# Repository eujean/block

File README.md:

Possibly over-engineered binary clock with temperature display.

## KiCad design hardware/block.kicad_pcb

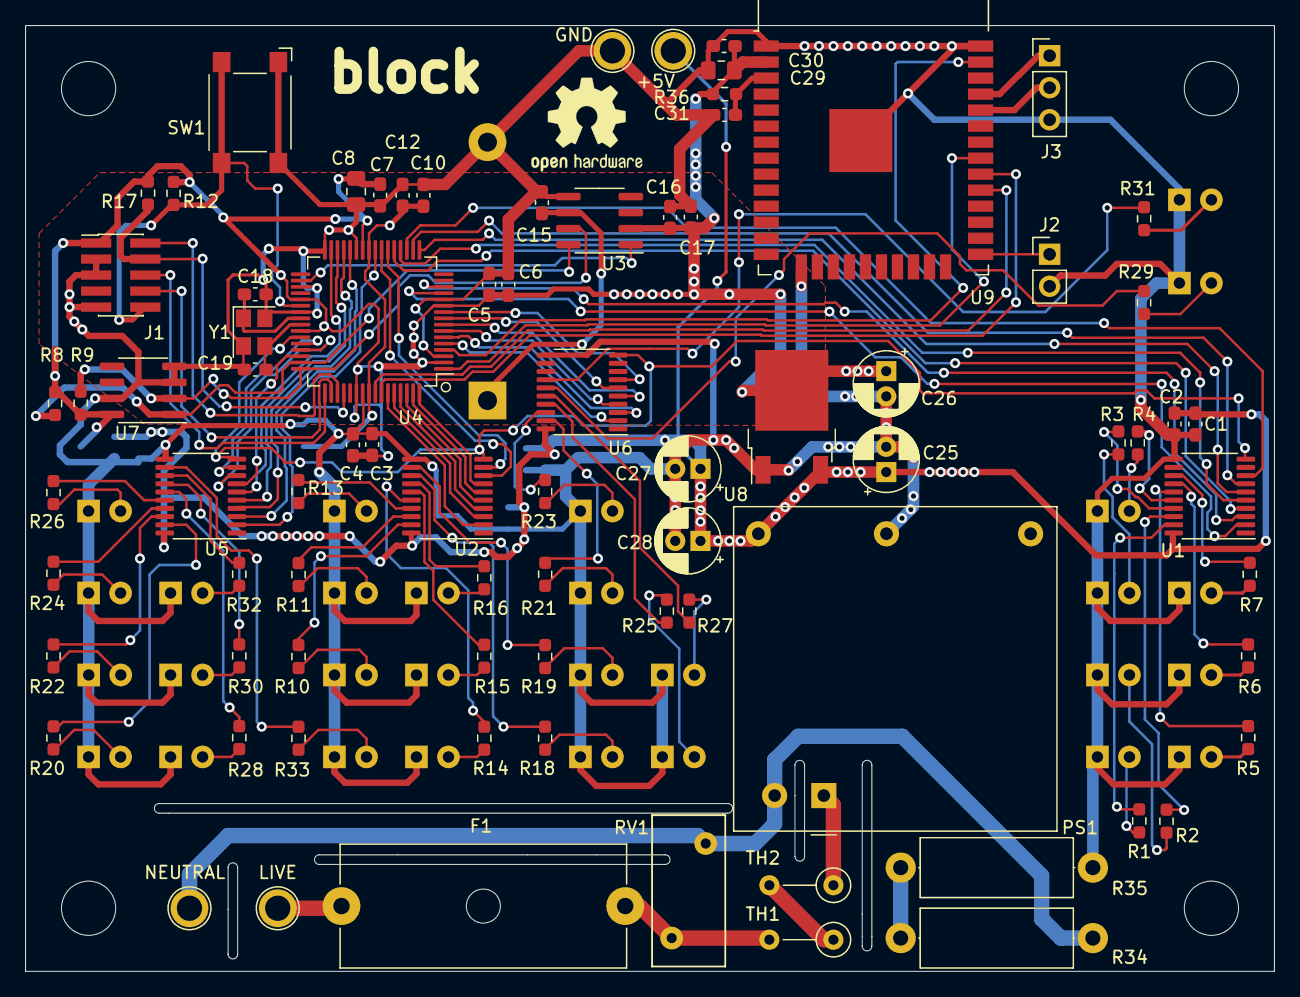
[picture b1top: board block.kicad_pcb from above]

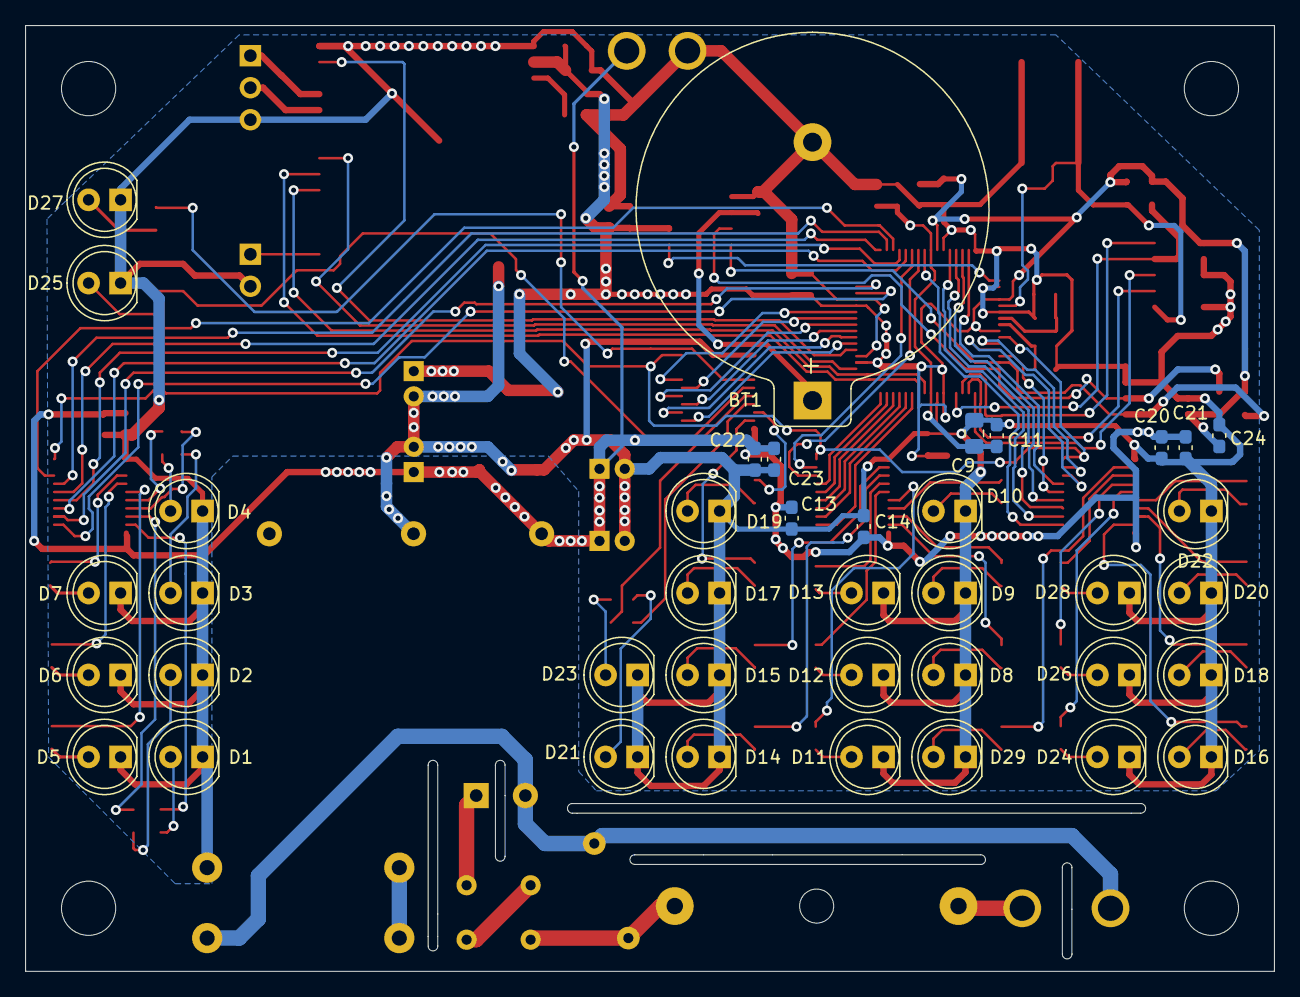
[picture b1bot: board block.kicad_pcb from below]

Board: 2 copper layers, 99.0 x 75.0 mm, 124 parts (39 on the bottom side), 117 nets.

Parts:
+5V: +5; TestPoint_Plated_Hole_D2.0mm
BT1: Battery_Cell; BatteryHolder_Keystone_106_1x20mm
C1, C10, C13, C17, C20, C22, C31: 1uF; C_0603_1608Metric_Pad1.08x0.95mm_HandSolder
C2, C3, C5, C7, C11, C12, C14, C15, C16, C21, C23, C24, C30: 0.1uF; C_0603_1608Metric_Pad1.08x0.95mm_HandSolder
C4, C6: 0.01uF; C_0603_1608Metric_Pad1.08x0.95mm_HandSolder
C8: 1uF; C_0805_2012Metric_Pad1.18x1.45mm_HandSolder
C9: 2.2uF; C_0805_2012Metric_Pad1.18x1.45mm_HandSolder
C18, C19: 10pF; C_0603_1608Metric_Pad1.08x0.95mm_HandSolder
C25, C28: 10uF; CP_Radial_D5.0mm_P2.00mm
C26: 100uF; CP_Radial_D5.0mm_P2.00mm
C27: 1.0uF; CP_Radial_D5.0mm_P2.00mm
C29: 10uF; C_0805_2012Metric_Pad1.18x1.45mm_HandSolder
D1, D2, D3, D4, D5, D6, D7, D8, D9, D10, D11, D12, D13, D14, D15, D16, D17, D18, D19, D20, D21, D22, D23, D24, D25, D26, D27, D28, D29: LED; LED_D5.0mm
F1: Fuse; Fuseholder_Cylinder-5x20mm_Schurter_0031_8201_Horizontal_Op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
GND: GND; TestPoint_Plated_Hole_D2.0mm
H1, H2, H3, H4: MountingHole; MountingHole_4.3mm_M4
J1: Conn_ARM_JTAG_SWD_10; PinHeader_2x05_P1.27mm_Vertical_SMD
J2: Conn_01x02_Female; PinHeader_1x02_P2.54mm_Vertical
J3: Conn_01x03; PinHeader_1x03_P2.54mm_Vertical
LIVE: LIVE; TestPoint_Plated_Hole_D2.0mm
NEUTRAL: NEUTRAL; TestPoint_Plated_Hole_D2.0mm
PS1: RAC05-05SK; Converter_ACDC_RECOM_RAC05-xxSK_THT
R1, R2, R3, R4, R5, R6, R7, R10, R11, R13, R14, R15, R16, R18, R19, R20, R21, R22, R23, R24, R25, R26, R27, R28, R29, R30, R31, R32, R33: R; R_0603_1608Metric_Pad0.98x0.95mm_HandSolder
R8, R9: 2.2k; R_0603_1608Metric_Pad0.98x0.95mm_HandSolder
R12, R17, R36: 10k; R_0603_1608Metric_Pad0.98x0.95mm_HandSolder
R34, R35: 560k; R_Axial_DIN0414_L11.9mm_D4.5mm_P15.24mm_Horizontal
RV1: Varistor; RV_Disc_D12mm_W5.8mm_P7.5mm
SW1: SW_Push4; SW_SPST_Omron_B3FS-100xP
TH1, TH2: 20R; R_Axial_DIN0207_L6.3mm_D2.5mm_P5.08mm_Vertical
U1, U2, U5, U6: TLC59213; TSSOP-20_4.4x6.5mm_P0.65mm
U3: DS3232M; SOIC-8_3.9x4.9mm_P1.27mm
U4: TM4C1231E6PM; LQFP-64_10x10mm_P0.5mm
U7: ADT7410; SOIC-8_3.9x4.9mm_P1.27mm
U8: LM1117-3.3; TO-252-2
U9: ESP32-WROOM-32
Y1: Crystal_GND24_Small; Crystal_SMD_Abracon_ABM8G-4Pin_3.2x2.5mm

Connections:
32kHz: U3.1, U4.34
+3V3: C3.1, C4.1, C5.1, C6.1, C7.1, C8.1, C16.1, C17.1, C24.1, C26.1, C29.1, C30.1, J1.1, R8.1, R9.1, R12.1, R17.1, R36.1, U3.2, U4.2, U4.11, U4.26, U4.37, U4.42, U4.54, U7.8, U8.2, U9.2
+5V: +5V.1, C1.1, C2.1, C13.1, C14.1, C20.1, C21.1, C22.1, C23.1, C25.1, C27.1, C28.1, PS1.5, U1.20, U2.20, U5.20, U6.20, U8.3
/Vddc: C9.1, C10.1, C11.1, C12.1, U4.25, U4.56
CS: U4.57, U9.29
GND: BT1.2, C1.2, C2.2, C3.2, C4.2, C5.2, C6.2, C7.2, C8.2, C9.2, C10.2, C11.2, C12.2, C13.2, C14.2, C15.2, C16.2, C17.2, C18.2, C19.2, C20.2, C21.2, C22.2, C23.2, C24.2, C25.2, C26.2, C27.2, C28.2, C29.2, C30.2, C31.2, D1.1, D2.1, D3.1, D4.1, D5.1, D6.1, D7.1, D8.1, D9.1, D10.1, D11.1, D12.1, D13.1, D14.1, D15.1, D16.1, D17.1, D18.1, D19.1, D20.1, D21.1, D22.1, D23.1, D24.1, D25.1, D26.1, D27.1, D28.1, D29.1, GND.1, J1.3, J1.5, J1.9, J2.2, J3.3, PS1.4, R35.1, SW1.1, SW1.2, U1.11, U2.11, U3.5, U4.3, U4.12, U4.27, U4.32, U4.35, U4.39, U4.55, U5.11, U6.11, U7.3, U7.4, U7.7, U8.1, U9.1, U9.15, U9.38, U9.39, Y1.2, Y1.4
HR01: U2.8, U4.23
HR02: U2.9, U4.22
HR04: U4.5, U6.2
HR08: U4.6, U6.3
HR11: U4.7, U6.4
HR12: U4.8, U6.5
I2C_SCL: R8.2, U3.8, U4.47, U7.1
I2C_SDA: R9.2, U3.7, U4.48, U7.2
LED_CLK: U1.10, U2.10, U4.43, U5.10, U6.10
MIN01: U4.44, U5.9
MIN02: U2.2, U4.59
MIN04: U2.3, U4.60
MIN08: U2.4, U4.61
MIN11: U2.5, U4.62
MIN12: U2.6, U4.63
MIN14: U2.7, U4.64
MISO: U4.1, U9.31
MOSI: U4.4, U9.37
unnamed: BT1.1, C15.1, U3.6
unnamed: C18.1, U4.40, Y1.1
unnamed: C19.1, U4.41, Y1.3
unnamed: C31.1, R36.2, U9.3
unnamed: D1.2, R1.1
unnamed: D2.2, R2.1
unnamed: D3.2, R3.1
unnamed: D4.2, R4.1
unnamed: D5.2, R5.1
unnamed: D6.2, R6.1
unnamed: D7.2, R7.1
unnamed: D8.2, R10.1
unnamed: D9.2, R11.1
unnamed: D10.2, R13.1
unnamed: D11.2, R14.1
unnamed: D12.2, R15.1
unnamed: D13.2, R16.1
unnamed: D14.2, R18.1
unnamed: D15.2, R19.1
unnamed: D16.2, R20.1
unnamed: D17.2, R21.1
unnamed: D18.2, R22.1
unnamed: D19.2, R23.1
unnamed: D20.2, R24.1
unnamed: D21.2, R25.1
unnamed: D22.2, R26.1
unnamed: D23.2, R27.1
unnamed: D24.2, R28.1
unnamed: D25.2, R29.1
unnamed: D26.2, R30.1
unnamed: D27.2, R31.1
unnamed: D28.2, R32.1
unnamed: D29.2, R33.1
unnamed: F1.1, RV1.1, TH1.2
unnamed: F1.2, LIVE.1
unnamed: J2.1, U9.25
unnamed: J3.1, U9.35
unnamed: J3.2, U9.34
unnamed: NEUTRAL.1, PS1.2, R34.2, RV1.2
unnamed: PS1.1, TH2.1
unnamed: R1.2, U1.19
unnamed: R2.2, U1.18
unnamed: R3.2, U1.17
unnamed: R4.2, U1.16
unnamed: R5.2, U1.15
unnamed: R6.2, U1.14
unnamed: R7.2, U1.13
unnamed: R10.2, U2.19
unnamed: R11.2, U2.18
unnamed: R13.2, U2.17
unnamed: R14.2, U2.16
unnamed: R15.2, U2.15
unnamed: R16.2, U2.14
unnamed: R18.2, U2.13
unnamed: R19.2, U2.12
unnamed: R20.2, U5.19
unnamed: R21.2, U6.19
unnamed: R22.2, U5.18
unnamed: R23.2, U6.18
unnamed: R24.2, U5.17
unnamed: R25.2, U6.17
unnamed: R26.2, U5.16
unnamed: R27.2, U6.16
unnamed: R28.2, U5.15
unnamed: R29.2, U6.15
unnamed: R30.2, U5.14
unnamed: R31.2, U6.14
unnamed: R32.2, U5.13
unnamed: R33.2, U5.12
unnamed: R34.1, R35.2
unnamed: TH1.1, TH2.2
POWER_LED: U4.10, U6.7
RESET: J1.10, R12.2, SW1.3, SW1.4, U4.38
SCLK: U4.58, U9.30
SEC01: U4.24, U5.2
SEC02: U4.28, U5.3
SEC04: U4.29, U5.4
SEC08: U4.30, U5.5
SEC11: U4.31, U5.6
SEC12: U4.46, U5.7
SEC14: U4.45, U5.8
STATUS_LED: U4.9, U6.6
TARGET_TCK: J1.4, R17.2, U4.52
TARGET_TDI: J1.8, U4.50
TARGET_TDO: J1.6, U4.49
TARGET_TMS: J1.2, U4.51
TEMP01: U1.2, U4.13
TEMP02: U1.3, U4.14
TEMP04: U1.4, U4.21
TEMP08: U1.5, U4.20
TEMP11: U1.6, U4.17
TEMP12: U1.7, U4.18
TEMP14: U1.8, U4.19
